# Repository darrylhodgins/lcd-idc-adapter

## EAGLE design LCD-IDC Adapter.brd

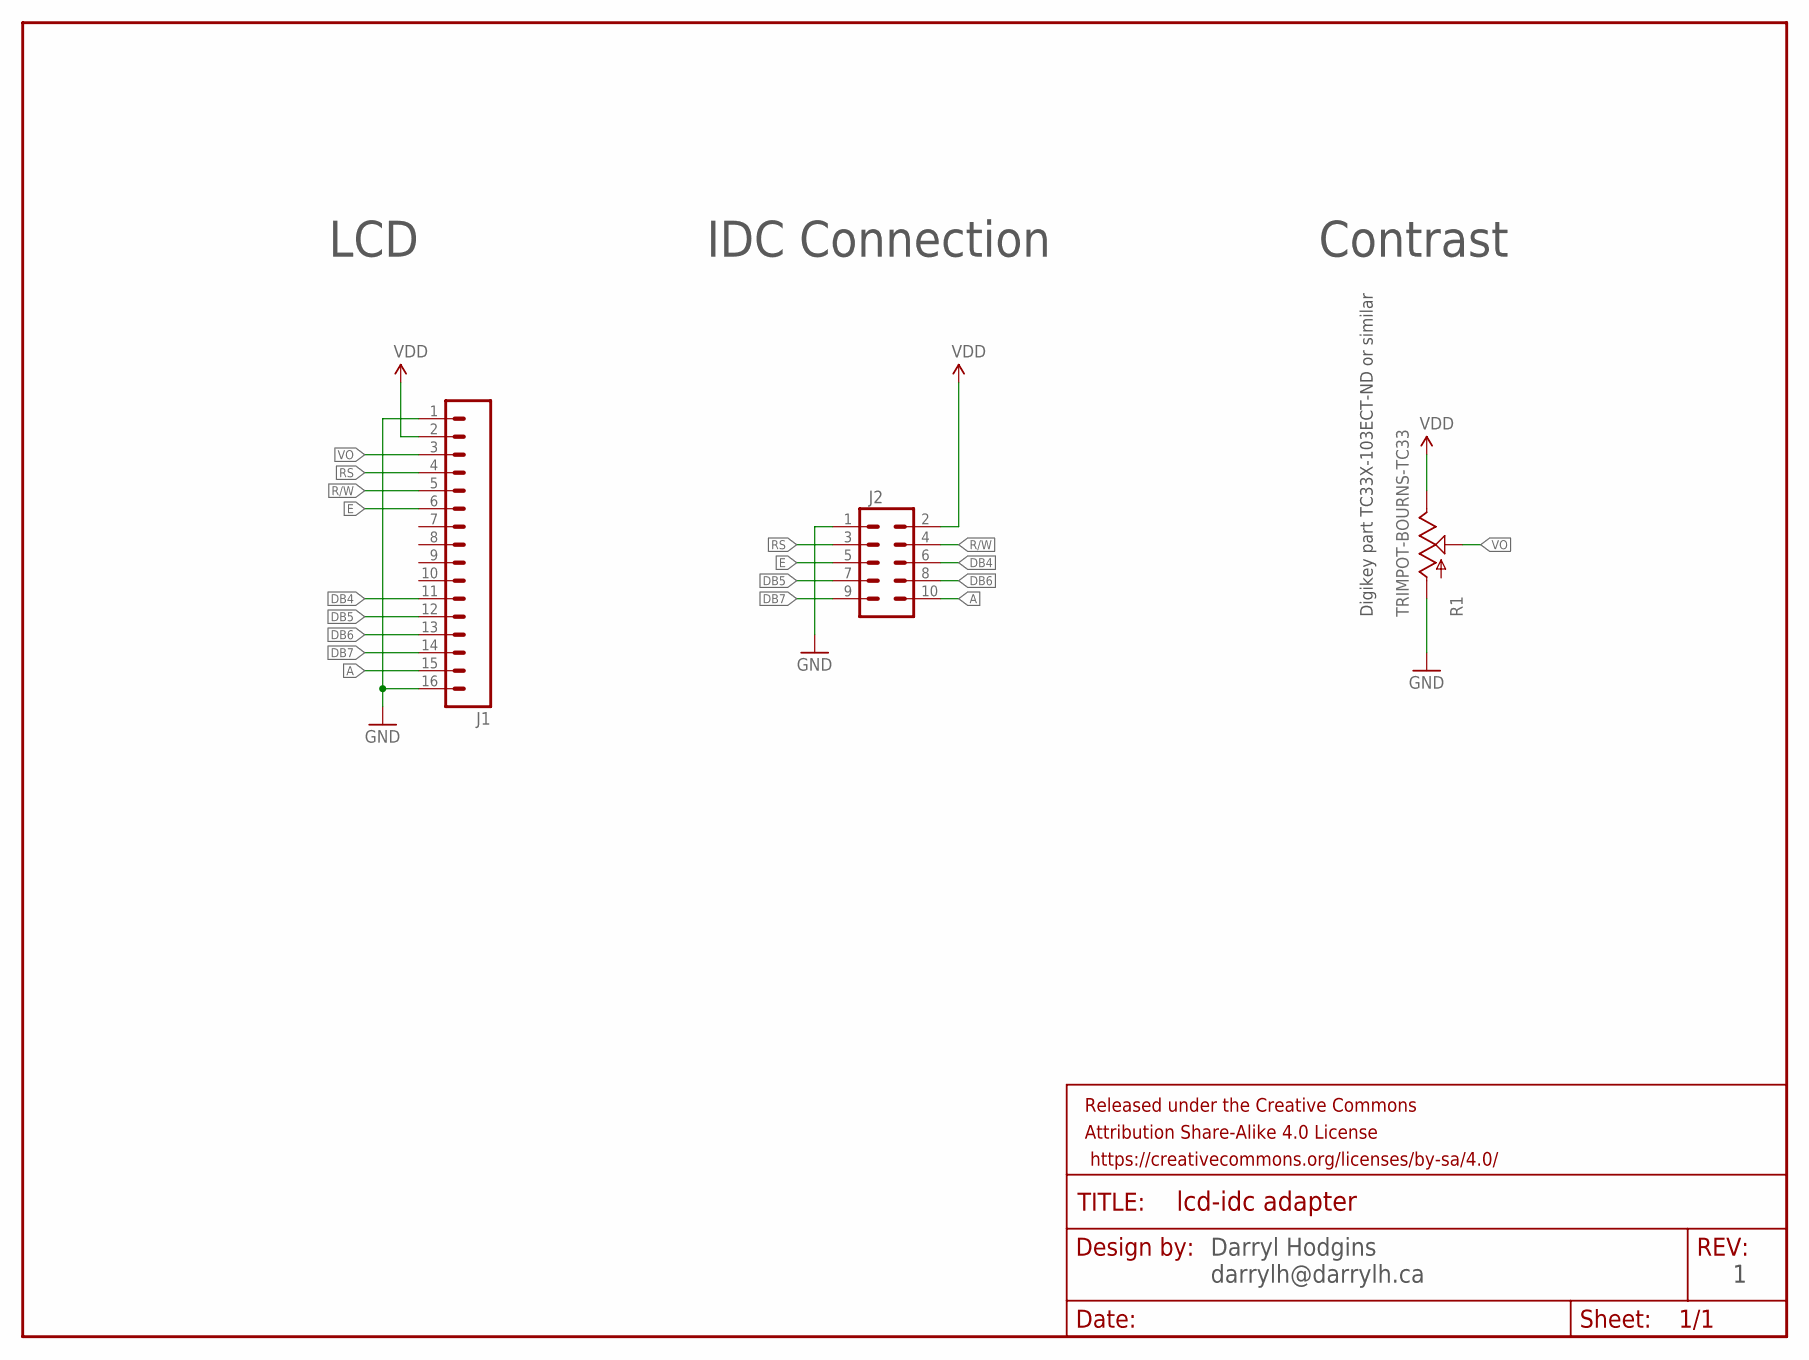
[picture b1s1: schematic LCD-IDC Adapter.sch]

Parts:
FRAME1: FRAME-LETTER; CREATIVE_COMMONS
J1: M16PTH; 1X16
J2: M05X2SHD; 2X5-SHROUDED
R1: TRIMPOT-BOURNS-TC33

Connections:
A: J1.15, J2.10
DB4: J1.11, J2.6
DB5: J1.12, J2.7
DB6: J1.13, J2.8
DB7: J1.14, J2.9
E: J1.6, J2.5
GND: J1.1, J1.16, J2.1, R1.1 (A)
R/W: J1.5, J2.4
RS: J1.4, J2.3
VDD: J1.2, J2.2, R1.3 (E)
VO: J1.3, R1.2 (S)

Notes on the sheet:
Digikey part TC33X-103ECT-ND or similar
LCD
IDC Connection
Contrast
Darryl Hodgins darrylh@darrylh.ca

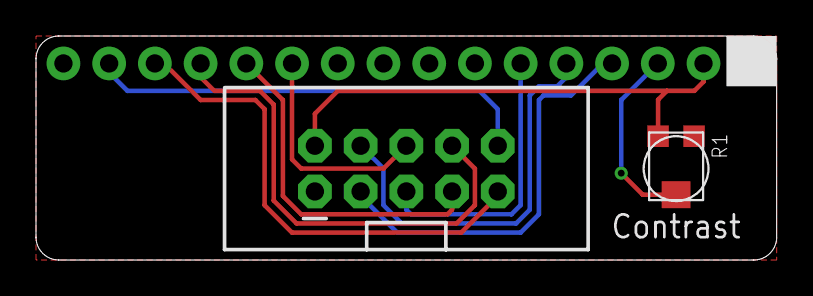
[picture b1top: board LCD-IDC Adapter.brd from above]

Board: 2 copper layers, 41.1 x 12.4 mm, 4 parts (1 on the bottom side), 11 nets.

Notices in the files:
parts and their libraries:
SparkFun-Connectors: Licensing: Creative Commons ShareAlike 4.0 International - https://creativecommons.org/licenses/by-sa/4.0
SparkFun-Aesthetics: Released under the Creative Commons Attribution Share-Alike 4.0 License
SparkFun-Aesthetics: https://creativecommons.org/licenses/by-sa/4.0
